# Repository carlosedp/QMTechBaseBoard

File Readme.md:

# QMTech Kintex 7 Motherboard

The objective of this project is to design a standard-size motherboard, initially in Mini-ITX size, to host dual Kintex 7 core boards from [QMTech](https://www.aliexpress.com/item/1005003668804223.html) and sold thru AliExpress.

The [QMTechBaseBoard](./QMTechBaseBoard-Kicad/) directory hosts Kicad files for the board design. We are still in draft phase and plan to close the design once the desired (and possible) peripherals have been defined.

The core board [manual](docs/QMTECH_Kintex-7_XC7K325T_Core_Board_User_Manual(Hardware)_V01.pdf) and [schematics](docs/QMTECH-XC7K325T-CORE-BOARD-V2-20211104.pdf) are provided. More information is available at <https://github.com/ChinaQMTECH/QMTECH_XC7K325T_CORE_BOARD>

Each QMTech Kintex 7 core board contains:

- Xilinx Kintex 7 XC7K325T FPGA
- 50Mhz crystal
- 256Mbit SPI Flash ([datasheet](docs/SPI/S25FL256L_S25FL128L_256-MB_32-MB_128-MB_16-MB_3.0_V_FL-L_FLASH_MEMORY.pdf)
- 256MB DDR3 RAM ([datasheet](docs/DDR3/2Gb_1_35V_DDR3L.pdf))
- 3 switches
- 4 LEDs
- JTAG Interface

## Project Plans

Initially we plan on getting feedback from the community about which features would be useful in a board like this. We expect getting the feedback thru Github [discussions](https://github.com/carlosedp/QMTechBaseBoard/discussions) or issues. If you have some suggestion for a part to be added, some additional feature or general idea, please [create a new topic](https://github.com/carlosedp/QMTechBaseBoard/discussions/new) describing it.

Also when defined, we need feedback from the community about which part/vendor to use. This is important since it's affected by availability and price.

## Peripherals

Some initial peripherals to be added:

- Dual Kintex7 Core-boards from QMTech
- 8x PMOD (4 PMOD for each core-board) (32 pins)
- Serial-USB - Quad FTDI (FT4232) - one UART, one JTAG for each core-board (2 pins)
- JTAG connection for each core-board to baseboard
- Dual 1Gbe RGMII, one for each core-board (8 pins)
- Dual USB OTG 2.0 port, one for each core-board (2 pins)
- Dual USB HID 2.0 port, one for each core-board (2 pins)
- Dual HDMI Out, one for each core-board (8 pins + 4 pins??*)
- VGA Out (single) (5 pins)
- 6 buttons for each core-board (6 pins)
- 4 switches for each core-board (4 pins)
- 8 LEDs for each core-board (8 pins)
- 2 RGB LED for each core-board (6 pins)
- Dual 7-pin SPI OLED (one for each board*) (5 pins)
- Dual microSD card connector (one for each board) (6 pins)
- Dual stereo audio connectors (one for each board) (4 pins)

Total IO per core-board: 99 GPIO, Above peripherals using 98 pins.

## Ideas

- Shared RAM?
- Shared Flash?
- SYZYGY?

## Parts

| Quantity | Description                  | Vendor | Part Number | Approx. Price | Source |
| -------- | ---------------------------- | ------ | ----------- | ------------- | ------ |
| 2        | RMGII Ethernet PHY           |        |             |               |        |
| 2        | Dual stacked USB connector   |        |             |               |        |
| 1        | MicroUSB connector           |        |             |               |        |
| 2        | Ethernet jack with magnetics |        |             |               |        |

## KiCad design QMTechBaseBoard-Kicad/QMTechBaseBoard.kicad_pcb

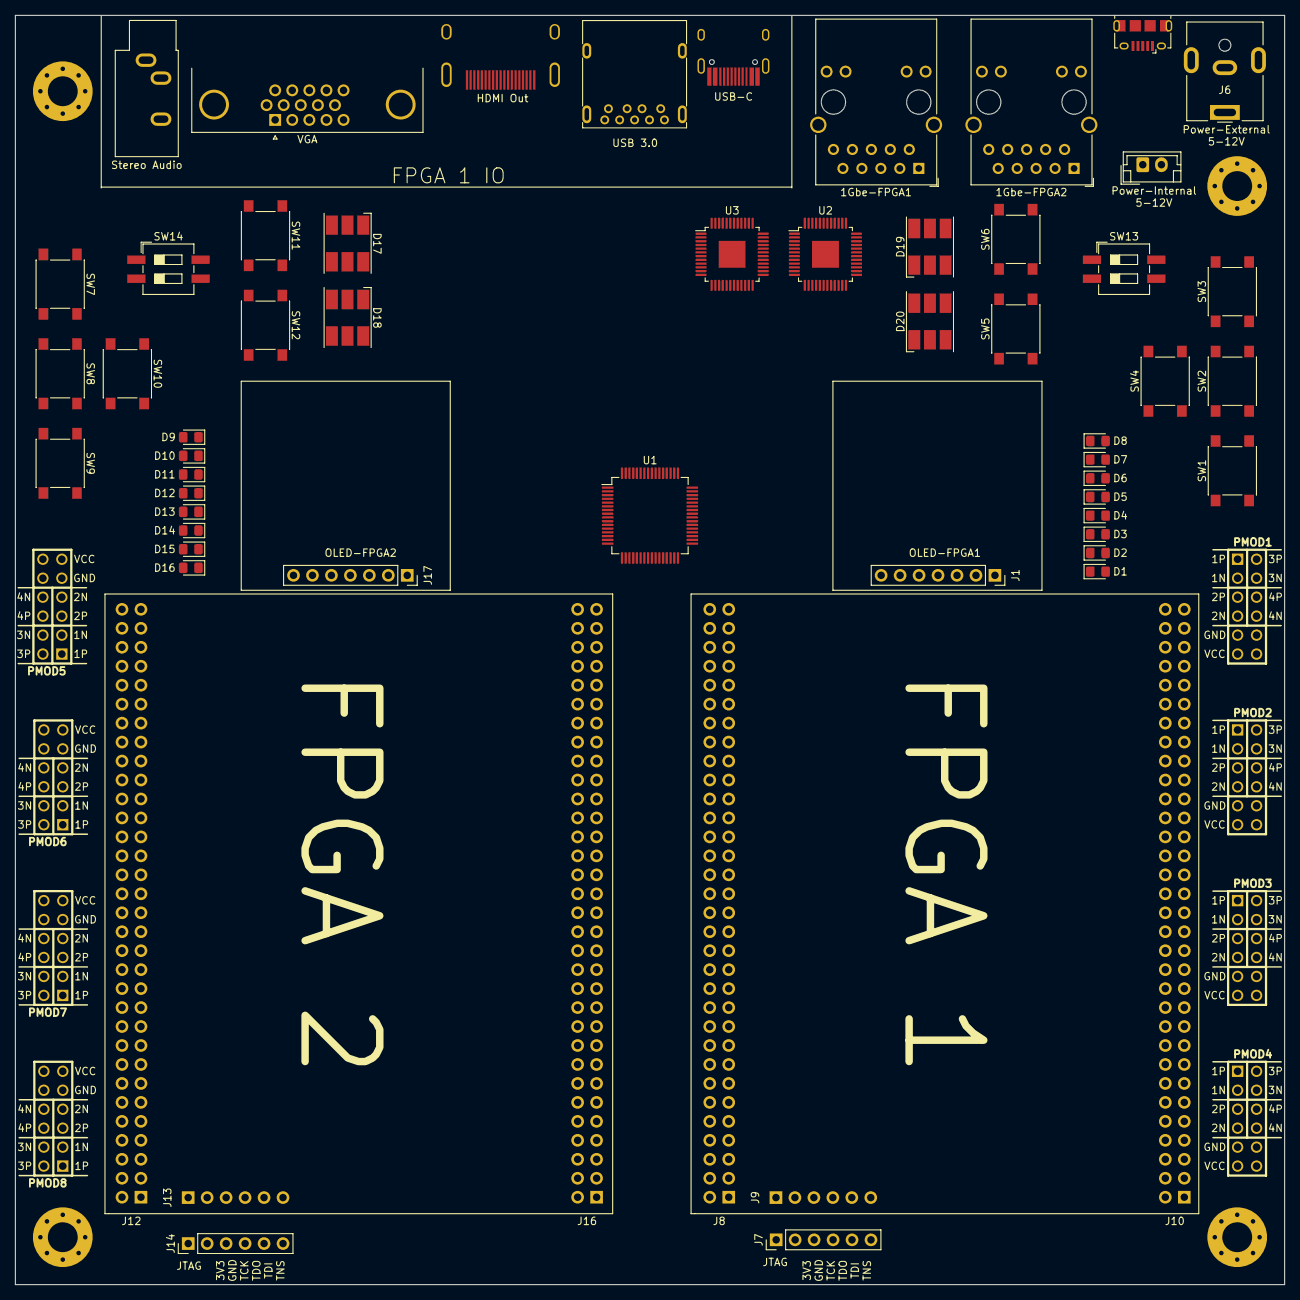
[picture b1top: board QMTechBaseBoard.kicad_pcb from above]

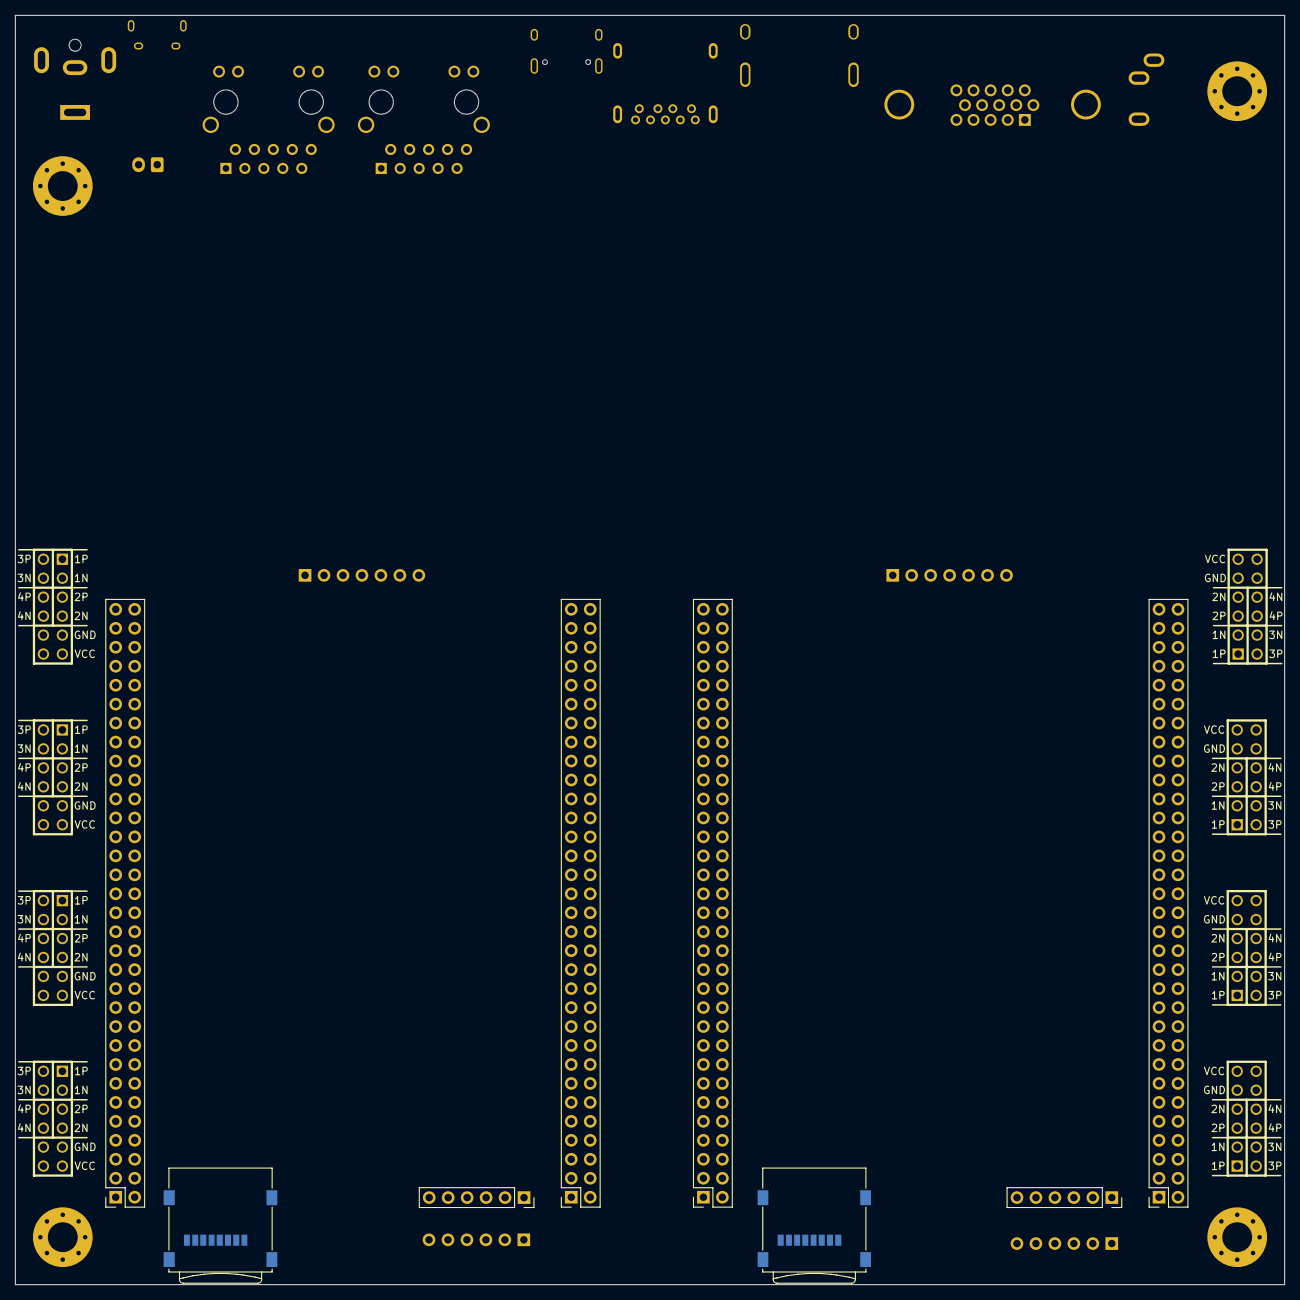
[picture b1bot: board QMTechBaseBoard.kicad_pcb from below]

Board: 2 copper layers, 170.0 x 170.0 mm, 67 parts (16 on the bottom side), 18 nets, no tracks yet.

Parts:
1Gbe-FPGA1: 1Gbe-FPGA1; RJ45_Wuerth_7499111446_Horizontal
1Gbe-FPGA2: 1Gbe-FPGA2; RJ45_Wuerth_7499111446_Horizontal
D1, D2, D3, D4, D5, D6, D7, D8, D9, D10, D11, D12, D13, D14, D15, D16: LED; LED_0805_2012Metric_Pad1.15x1.40mm_HandSolder
D17, D18, D19, D20: LED_ABGR; LED_RGB_Cree-PLCC-6_6x5mm_P2.1mm
HDMI Out: HDMI_A_1.4; HDMI_15mm
J1: OLED-FPGA1; PinSocket_1x07_P2.54mm_Vertical
J3: Stereo Audio; Jack_3.5mm_CUI_SJ1-3533NG_Horizontal
J5: Power-Internal; JST_EH_B2B-EH-A_1x02_P2.50mm_Vertical
J6: Power-External; BarrelJack_CUI_PJ-063AH_Horizontal
J7: JTAG-FPGA1; PinHeader_1x06_P2.54mm_Vertical
J8, J10, J12, J16: Conn_02x32_Odd_Even; PinSocket_2x32_P2.54mm_Vertical
J9, J13: Conn_01x06_Female; PinSocket_1x06_P2.54mm_Vertical
J11, J15: Micro_SD_Card; microSD_HC_Wuerth_693072010801
J14: JTAG-FPGA2; PinHeader_1x06_P2.54mm_Vertical
J17: OLED-FPGA2; PinSocket_1x07_P2.54mm_Vertical
J21: UART-JTAG; USB_Micro-B_Amphenol_10118194_Horizontal
PMOD1, PMOD2, PMOD3, PMOD4, PMOD5, PMOD6, PMOD7, PMOD8: PMOD-Host-x2-GPIO; pmod_pin_array_6x2_hs
SW1, SW2, SW3, SW4, SW5, SW6, SW7, SW8, SW9, SW10, SW11, SW12: SW_Push; SW_SPST_PTS645
SW13, SW14: SW_DIP_x02; SW_DIP_SPSTx02_Slide_6.7x6.64mm_W8.61mm_P2.54mm_LowProfile
U1: FT4232H; LQFP-64_10x10mm_P0.5mm
U2, U3: RTL8211EG-VB-CG; LQFP-48-1EP_7x7mm_P0.5mm_EP3.6x3.6mm
USB 3.0: USB3_A; USB3_A_Molex_48393-001
USB-C: USB_C_Plug; HRO-TYPE-C-31-M-12-HandSoldering
VGA: DB15_Female_HighDensity; DSUB-15-HD_Female_Horizontal_P2.29x1.98mm_EdgePinOffset3.03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

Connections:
+3V3: J8.3, J8.4, J12.3, J12.4
+5V: J8.63, J8.64, J10.63, J10.64, J12.63, J12.64, J16.63, J16.64
GND: J8.1, J8.2, J8.5, J8.6, J8.61, J8.62, J10.1, J10.2, J10.5, J10.6, J10.61, J10.62, J12.1, J12.2, J12.5, J12.6, J12.61, J12.62, J16.1, J16.2, J16.5, J16.6, J16.61, J16.62
unnamed: J7.1, J9.1
unnamed: J7.2, J9.2
unnamed: J7.3, J9.3
unnamed: J7.4, J9.4
unnamed: J7.5, J9.5
unnamed: J7.6, J9.6
unnamed: J13.1, J14.1
unnamed: J13.2, J14.2
unnamed: J13.3, J14.3
unnamed: J13.4, J14.4
unnamed: J13.5, J14.5
unnamed: J13.6, J14.6
unnamed: U2.2, U2.4
unnamed: U3.2, U3.4
VCC: J10.3, J10.4, J16.3, J16.4

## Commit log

2022-08-24 Initial import for docs and board layout
2022-08-24 Create LICENSE
2022-08-24 Add discussions link
2022-08-24 Fix some text. Update draft board render
